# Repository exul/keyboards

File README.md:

# Disclaimer

The files in this repository are meant as inspiration for others who want to build a keyboard from scratch as well. You can build the keyboard yourself with the files provided here, but be aware that it's not beginner friendly. The MCU is soldered directly onto the PCB, the power connection from the PCB to the XIAO needs to be soldered manually, there is no reset button (you'll need to short GND and RST on the exposed XIAO) and the battery is soldered directly onto the PCB as well. When opening the PCB in KiCAD and running the Design Rule Checker it complains about two not connected components, this is because they have to be soldered manually, and I couldn't figure out how to fix this in KiCAD.
The config makes use of custom footprints, meaning that it won't work with the web version of Ergogen.

# My keyboard journey

 I've used ergonomic keyboards for more than 10 years, both prebuilt ones and keyboards I designed and built myself. I've documented my experience so that others can draw some inspiration from it. Depending on what you're planning to do, different chapters might be of interest to you.

1. [How  it all started: The prebuilt keyboards I used and my experience with them](docs/prebuilt_keyboards.md)
2. [Building my own keyboard from scratch](docs/from_scratch.md)

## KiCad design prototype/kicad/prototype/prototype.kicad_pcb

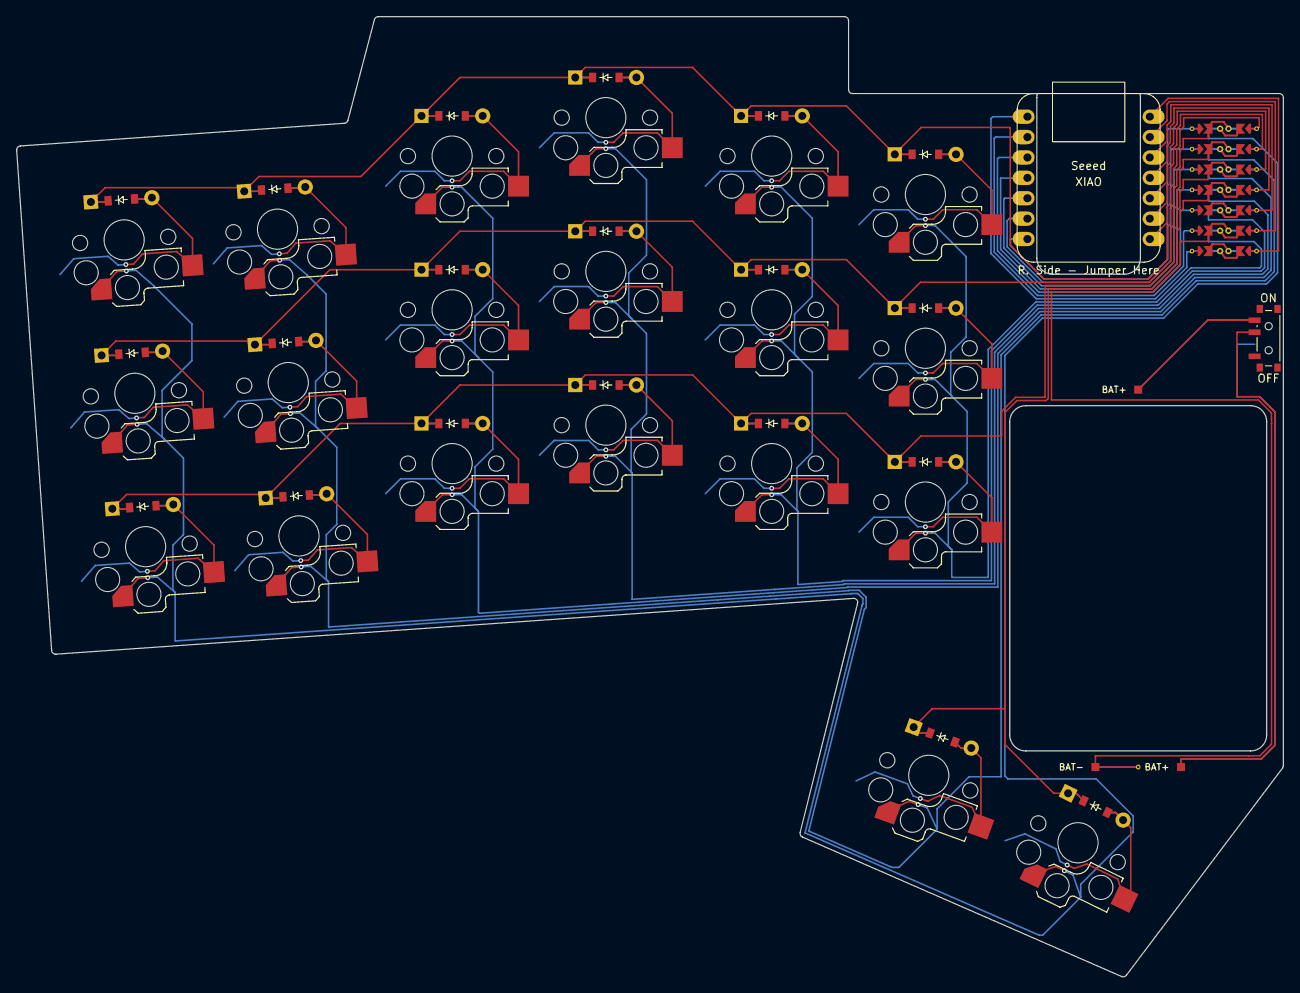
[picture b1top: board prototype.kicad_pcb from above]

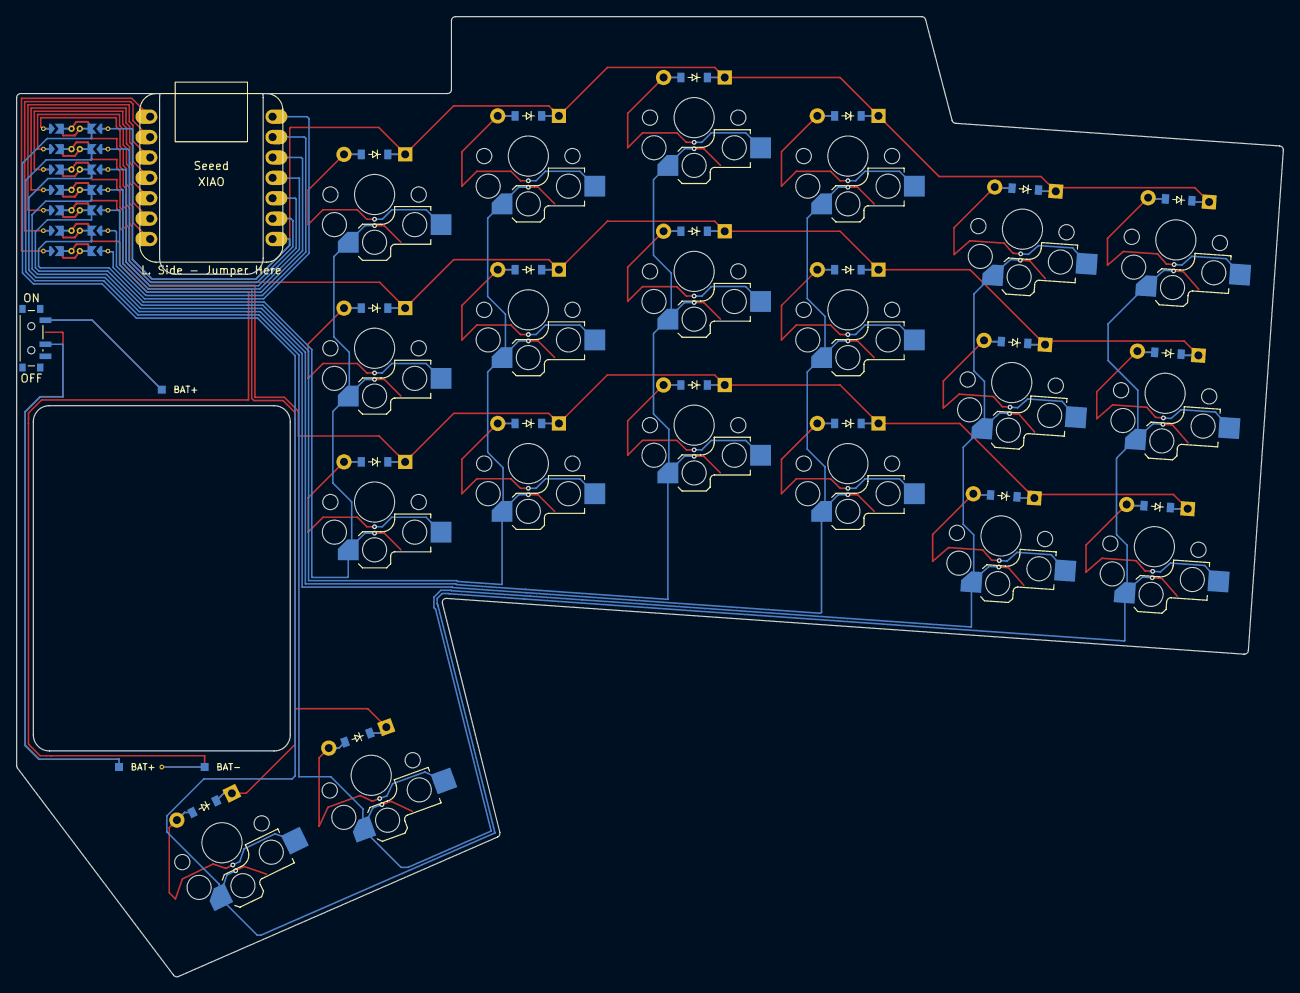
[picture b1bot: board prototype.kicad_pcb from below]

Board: 2 copper layers, 157.8 x 119.6 mm, 44 parts (20 on the bottom side), 32 nets.

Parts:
D1, D2, D3, D4, D5, D6, D7, D8, D9, D10, D11, D12, D13, D14, D15, D16, D17, D18, D19, D20: ComboDiode
PAD1, PAD2, PAD3: SMDPad
PWR1: power_switch_smd_side
S1, S2, S3, S4, S5, S6, S7, S8, S9, S10, S11, S12, S13, S14, S15, S16, S17, S18, S19, S20: switch_choc_v1_v2

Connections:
BAT+: PAD1.1, PWR1.1, PWR1.3
P1: S16.1, S17.1, S18.1
P2: S13.1, S14.1, S15.1
P3: S10.1, S11.1, S12.1
P4: S7.1, S8.1, S9.1
P5: S4.1, S5.1, S6.1, S19.1
P6: S1.1, S2.1, S3.1, S20.1
P7: D3.1, D6.1, D9.1, D12.1, D15.1, D18.1
P8: D2.1, D5.1, D8.1, D11.1, D14.1, D17.1
P9: D1.1, D4.1, D7.1, D10.1, D13.1, D16.1
P10: D19.1, D20.1
RAW: PAD2.1, PWR1.2
home_cluster: D19.2, S19.2
index_bottom: D13.2, S13.2
index_home: D14.2, S14.2
index_top: D15.2, S15.2
inner_bottom: D16.2, S16.2
inner_home: D17.2, S17.2
inner_top: D18.2, S18.2
middle_bottom: D10.2, S10.2
middle_home: D11.2, S11.2
middle_top: D12.2, S12.2
outer_bottom: D1.2, S1.2
outer_cluster: D20.2, S20.2
outer_home: D2.2, S2.2
outer_top: D3.2, S3.2
pinky_bottom: D4.2, S4.2
pinky_home: D5.2, S5.2
pinky_top: D6.2, S6.2
ring_bottom: D7.2, S7.2
ring_home: D8.2, S8.2
ring_top: D9.2, S9.2

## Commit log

2024-11-10 init
2024-12-01 add output
    first working version
2024-12-10 reversible
2025-02-09 Update reame
2025-04-30 add v2
2025-05-23 switch to Seeed Xiao
2025-06-16 prototype thin version
2025-06-27 prototype thin version built
2025-08-23 more readme
2025-11-14 more space
2025-11-23 next version
2025-12-21 cleanup
2025-12-26 improve case
2025-12-26 improve thumb cluster position
2025-12-26 add kicad files
2025-12-26 adjust thumb cluster
2025-12-26 new footprint folder
2025-12-26 latest pcb
2026-01-01 update case
2026-01-02 fix right case bottom
2026-01-03 add latest pcb
2026-01-08 readme update
2026-01-08 minor case fix
2026-01-09 add output files
2026-01-09 add disclaimer
2026-01-09 add license
2026-01-11 split text into chapters
